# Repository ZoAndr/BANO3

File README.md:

# BANO3
Board Aviation Anticollision Navigation Lights Version 3

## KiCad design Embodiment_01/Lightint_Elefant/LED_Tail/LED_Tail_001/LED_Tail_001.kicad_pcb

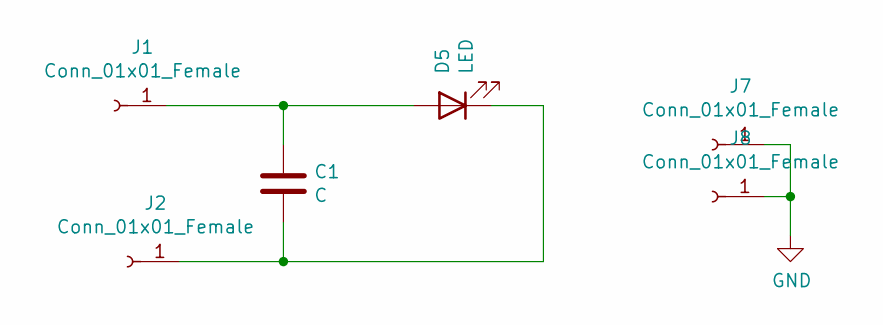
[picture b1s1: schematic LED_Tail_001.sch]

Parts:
C1: C; C_0805_2012Metric_Pad1.18x1.45mm_HandSolder
D5: LED; LED_Cree-XHP35
J1, J2: Conn_01x01_Female; pin_0.8
J7, J8: Conn_01x01_Female; pin_1.5

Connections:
GND: J7.1, J8.1
unnamed: C1.1, D5.2 (A), J1.1
unnamed: C1.2, D5.1 (K), J2.1

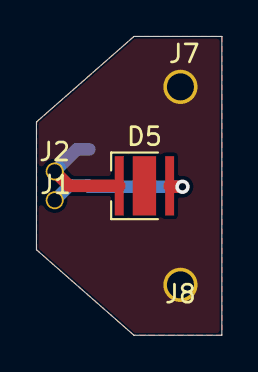
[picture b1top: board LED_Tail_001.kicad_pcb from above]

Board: 2 copper layers, 10.3 x 16.6 mm, 6 parts (1 on the bottom side), 3 nets.

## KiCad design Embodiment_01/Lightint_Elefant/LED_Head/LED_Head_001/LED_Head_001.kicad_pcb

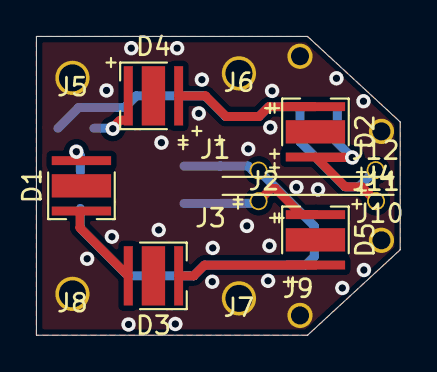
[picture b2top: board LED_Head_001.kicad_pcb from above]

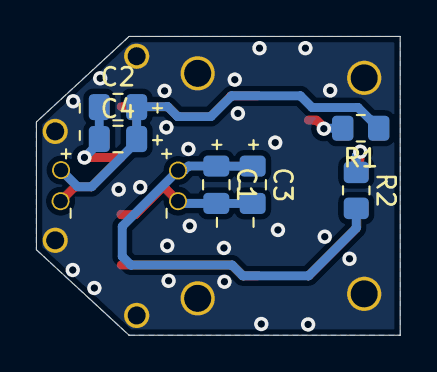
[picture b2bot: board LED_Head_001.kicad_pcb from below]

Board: 2 copper layers, 20.2 x 16.6 mm, 23 parts (6 on the bottom side), 10 nets.

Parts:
C1, C2, C3, C4: C; C_0805_2012Metric_Pad1.18x1.45mm_HandSolder
D1, D2, D3, D4, D5: LED; LED_Cree-XHP35
J1, J2, J11, J12: Conn_01x01_Female; pin_0.8
J3, J4, J9, J10: Conn_01x01_Female; pin_1.0
J5, J6, J7, J8: Conn_01x01_Female; pin_1.5
R1, R2: R; R_0805_2012Metric_Pad1.20x1.40mm_HandSolder

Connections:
GND: J3.1, J4.1, J5.1, J6.1, J7.1, J8.1, J9.1, J10.1
unnamed: C1.1, C3.1, J1.1, R2.2
unnamed: C1.2, C3.2, D5.1, J2.1
unnamed: C2.1, C4.1, D2.2, J11.1
unnamed: C2.2, C4.2, J12.1, R1.1
unnamed: D1.1, D3.2
unnamed: D1.2, R2.1
unnamed: D2.1, D4.2
unnamed: D3.1, D5.2
unnamed: D4.1, R1.2

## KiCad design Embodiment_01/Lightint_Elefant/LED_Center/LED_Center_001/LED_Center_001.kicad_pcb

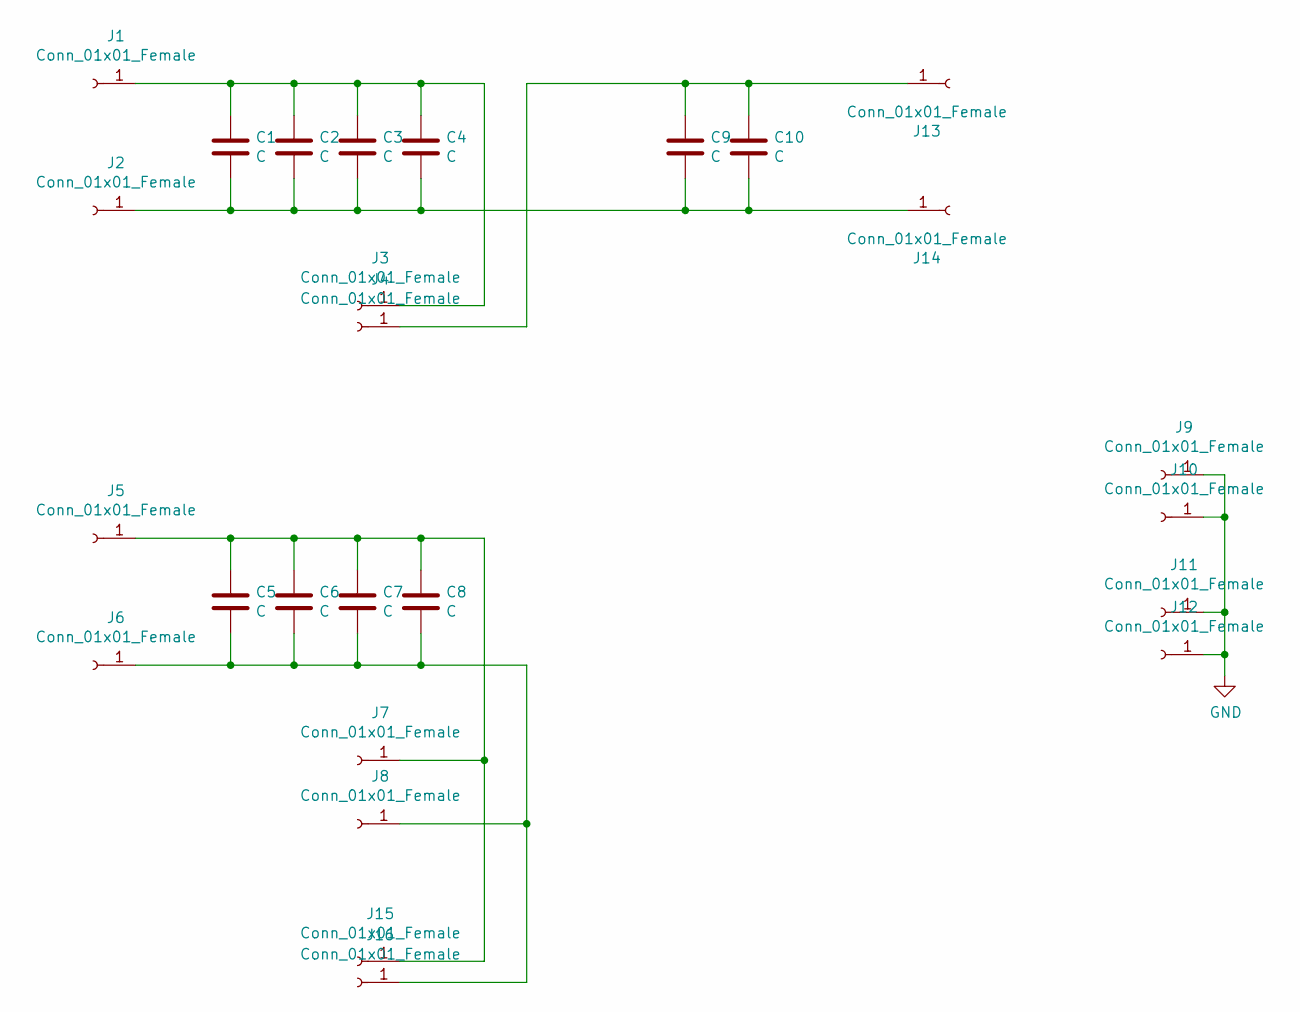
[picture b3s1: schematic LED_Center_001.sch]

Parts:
C1, C2, C3, C4, C5, C6, C7, C8, C9, C10: C; C_0805_2012Metric_Pad1.18x1.45mm_HandSolder
J1, J2, J5, J6, J13, J14: Conn_01x01_Female; WireSidePlate_001
J3, J4, J7, J8, J15, J16: Conn_01x01_Female; pin_0.8
J9, J10, J11, J12: Conn_01x01_Female; pin_1.0

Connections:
GND: J9.1, J10.1, J11.1, J12.1
unnamed: C1.1, C2.1, C3.1, C4.1, J1.1, J3.1
unnamed: C1.2, C2.2, C3.2, C4.2, C9.2, C10.2, J2.1, J14.1
unnamed: C5.1, C6.1, C7.1, C8.1, J5.1, J7.1, J15.1
unnamed: C5.2, C6.2, C7.2, C8.2, J6.1, J8.1, J16.1
unnamed: C9.1, C10.1, J4.1, J13.1

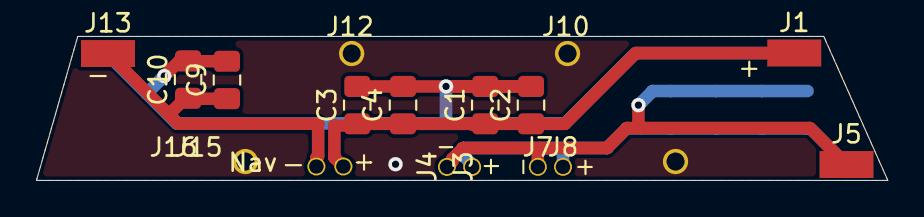
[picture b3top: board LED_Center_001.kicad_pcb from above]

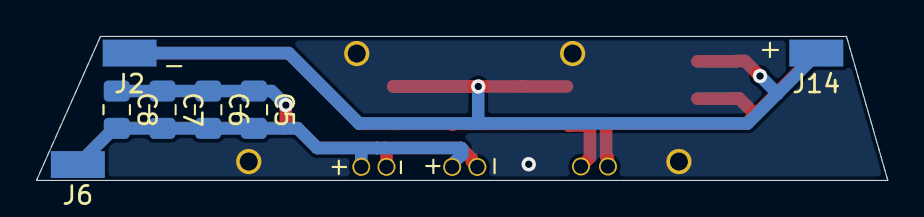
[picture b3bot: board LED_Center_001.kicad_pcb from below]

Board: 2 copper layers, 47.3 x 8.0 mm, 26 parts (7 on the bottom side), 6 nets.

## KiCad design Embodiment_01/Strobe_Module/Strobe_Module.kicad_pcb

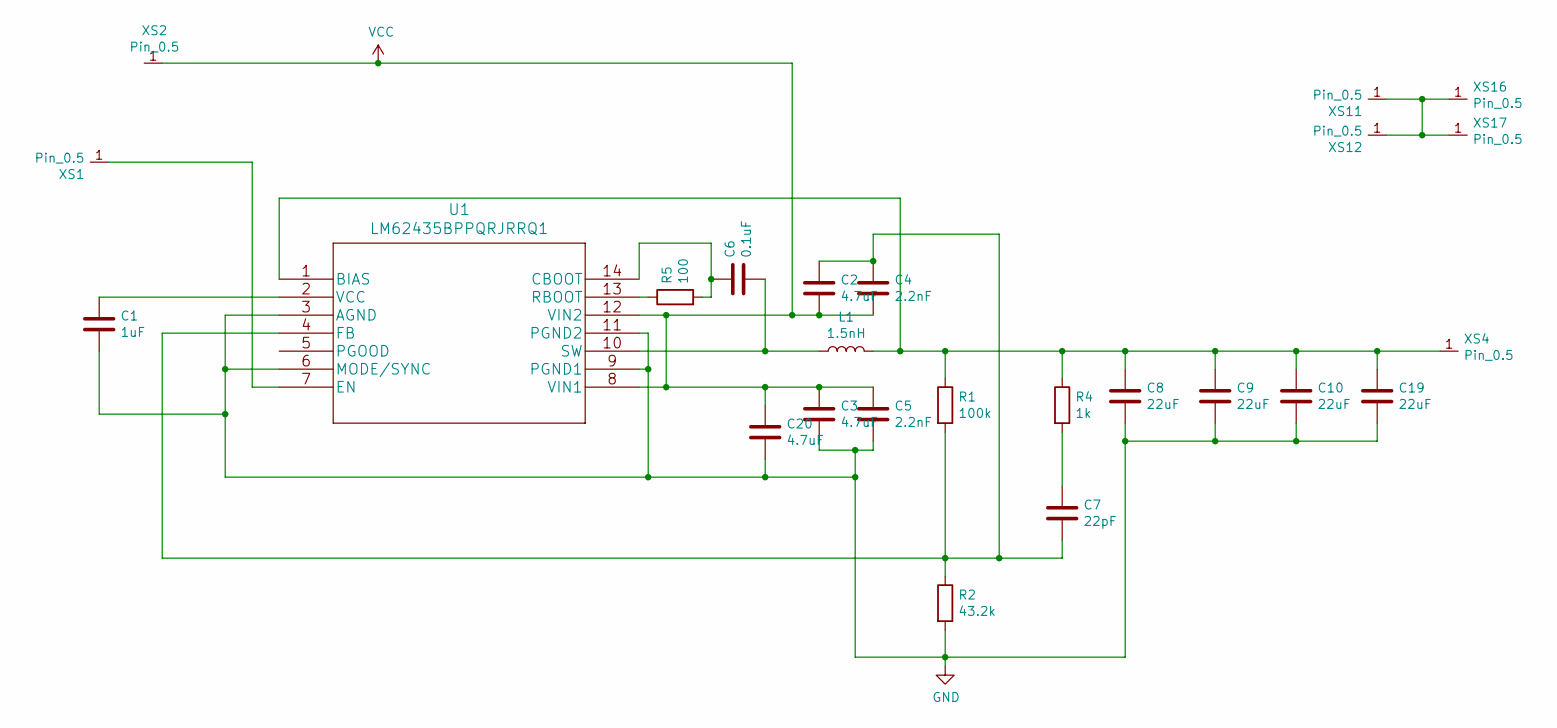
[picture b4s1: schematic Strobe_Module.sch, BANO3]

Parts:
C1: 1uF; C_0603_1608Metric
C2, C3, C20: 4.7uF; C_0805_2012Metric
C4, C5: 2.2nF; C_0603_1608Metric
C6: 0.1uF; C_0603_1608Metric
C7: 22pF; C_0603_1608Metric
C8, C9, C10, C19: 22uF; C_0805_2012Metric
L1: 1.5nH; L_Bourns-SRN6028
R1: 100k; R_0603_1608Metric
R2: 43.2k; R_0603_1608Metric
R4: 1k; R_0603_1608Metric
R5: 100; R_0603_1608Metric
U1: LM62435BPPQRJRRQ1
XS1, XS2, XS4, XS11, XS12, XS16, XS17: Pin_0.5; pin_0.8

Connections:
GND: C1.2, C3.2, C5.2, C8.2, C9.2, C10.2, C19.2, C20.2, R2.2, U1.3 (AGND), U1.6 (MODE/SYNC), U1.9 (PGND1), U1.11 (PGND2)
unnamed: C1.1, U1.2 (VCC)
unnamed: C2.1, C4.1, C7.2, R1.2, R2.1, U1.4 (FB)
unnamed: C6.1, R5.2, U1.14 (CBOOT)
unnamed: C6.2, L1.1, U1.10 (SW)
unnamed: C7.1, R4.2
unnamed: C8.1, C9.1, C10.1, C19.1, L1.2, R1.1, R4.1, U1.1 (BIAS), XS4.1
unnamed: R5.1, U1.13 (RBOOT)
unnamed: U1.7 (EN), XS1.1
unnamed: XS11.1, XS12.1, XS16.1, XS17.1
VCC: C2.2, C3.1, C4.2, C5.1, C20.1, U1.8 (VIN1), U1.12 (VIN2), XS2.1

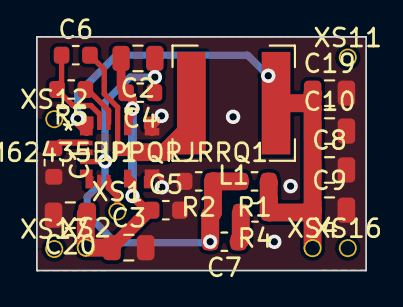
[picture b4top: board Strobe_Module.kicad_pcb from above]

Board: 2 copper layers, 18.3 x 13.0 mm, 25 parts (0 on the bottom side), 11 nets.

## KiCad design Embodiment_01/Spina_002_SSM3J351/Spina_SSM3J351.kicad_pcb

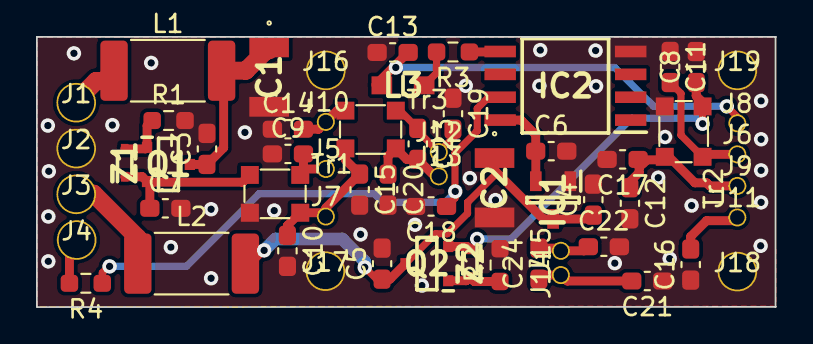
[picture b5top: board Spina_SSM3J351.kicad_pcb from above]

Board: 2 copper layers, 41.0 x 15.0 mm, 59 parts (0 on the bottom side), 25 nets.

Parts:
C1, C2: C; C3225_Commercial
C3, C4, C5, C6, C7, C8, C9, C10, C11, C12, C13, C14, C15, C16, C17, C18, C19, C20, C21, C22, C23, C24: C; C_0603_1608Metric_Pad1.08x0.95mm_HandSolder
IC1: ZXTR2105FQ-7; SOT96P240X110-3N
IC2: ATTINY25-20SH; SOIC127P798X216-8N
J1, J2, J3, J4, J16, J17, J18, J19: Conn_01x01; pin_2.0
J5, J6, J7, J8, J9, J10, J11, J12, J13, J14, J15: Conn_01x01; pin_0.8
L1, L2: SNR6045K-1R0N; L_2512_6332Metric_Pad1.52x3.35mm_HandSolder
L3: L; LQM21DN220N00L
Q1, Q2: SSM3J351R,LF; SOTFL95P240X88-3N
R1, R2, R3, R4: R; R_0603_1608Metric_Pad0.98x0.95mm_HandSolder
Tr1, Tr2, Tr3: CMF3225
Z1, Z2: BZT52C12TQ-7-F; SODFL1608X65N

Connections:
GND: C1.2, C2.2, C3.2, C4.2, C5.2, C6.2, C7.2, C8.2, C9.1, C10.2, C11.1, C12.2, C13.1, C14.1, C15.2, C16.1, C17.2, C18.2, C19.1, C20.2, C21.1, C22.2, IC1.1, IC2.4, J2.1, J16.1, J17.1, J18.1, J19.1, R1.2, R2.2, Tr1.2, Tr2.2
GND1: C12.1, C17.1, J9.1, Tr2.4
GND2: C22.1, C24.2, J15.1
GND3: C10.1, C15.1, J7.1, Tr1.4, Tr3.2
GNDA: C20.1, C23.2, J13.1, Tr3.4
unnamed: C1.1, C3.1, L1.2, Q1.3
unnamed: C2.1, C4.1, C5.1, IC1.3, L2.2, Q2.3
unnamed: C6.1, IC1.2, IC2.8
unnamed: C7.1, Q1.2, Tr1.1, Z1.1
unnamed: C8.1, Q2.2, Tr2.1, Z2.1
unnamed: C9.2, J5.1, Tr1.3
unnamed: C11.2, J6.1, Tr2.3
unnamed: C13.2, J8.1, L3.2
unnamed: C14.2, J10.1, Tr3.1
unnamed: C16.2, J11.1
unnamed: C18.1, IC2.7, R4.1
unnamed: C19.2, C23.1, J12.1, Tr3.3
unnamed: C21.2, C24.1, J14.1
unnamed: IC2.5, R3.1
unnamed: J1.1, L1.1
unnamed: J3.1, L2.1
unnamed: J4.1, R4.2
unnamed: L3.1, R3.2
unnamed: Q1.1, R1.1, Z1.2
unnamed: Q2.1, R2.1, Z2.2

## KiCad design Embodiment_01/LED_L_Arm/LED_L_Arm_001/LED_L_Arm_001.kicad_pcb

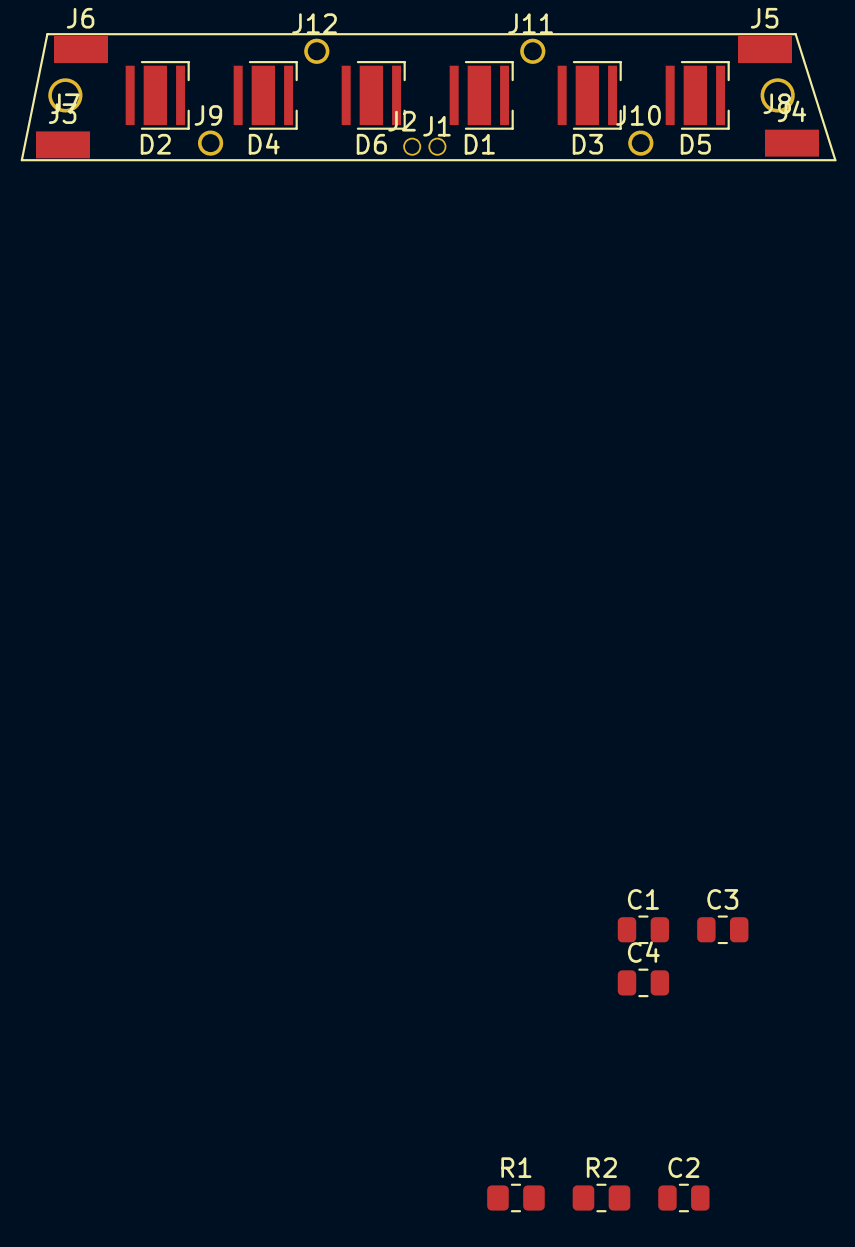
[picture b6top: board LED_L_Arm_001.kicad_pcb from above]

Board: 2 copper layers, 24 parts (0 on the bottom side), 9 nets, no tracks yet.

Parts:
C1, C2, C3, C4: C; R_0805_2012Metric
D1, D2, D3, D4, D5, D6: LED; LED_Cree-XHP35
J1, J2: Conn_01x01_Female; pin_0.8
J3, J4, J5, J6: Conn_01x01_Female; WireSidePlate_001
J7, J8: Conn_01x01_Female; pin_1.5
J9, J10, J11, J12: Conn_01x01_Female; pin_1.0
R1, R2: R; R_0805_2012Metric_Pad1.20x1.40mm_HandSolder

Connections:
GND: J3.1, J4.1, J5.1, J6.1, J7.1, J8.1, J9.1, J10.1, J11.1, J12.1
unnamed: C1.1, C2.1, C3.1, C4.1, D1.2, D2.2, J1.1
unnamed: C1.2, C2.2, C3.2, C4.2, J2.1, R1.1, R2.1
unnamed: D1.1, D3.2
unnamed: D2.1, D4.2
unnamed: D3.1, D5.2
unnamed: D4.1, D6.2
unnamed: D5.1, R1.2
unnamed: D6.1, R2.2

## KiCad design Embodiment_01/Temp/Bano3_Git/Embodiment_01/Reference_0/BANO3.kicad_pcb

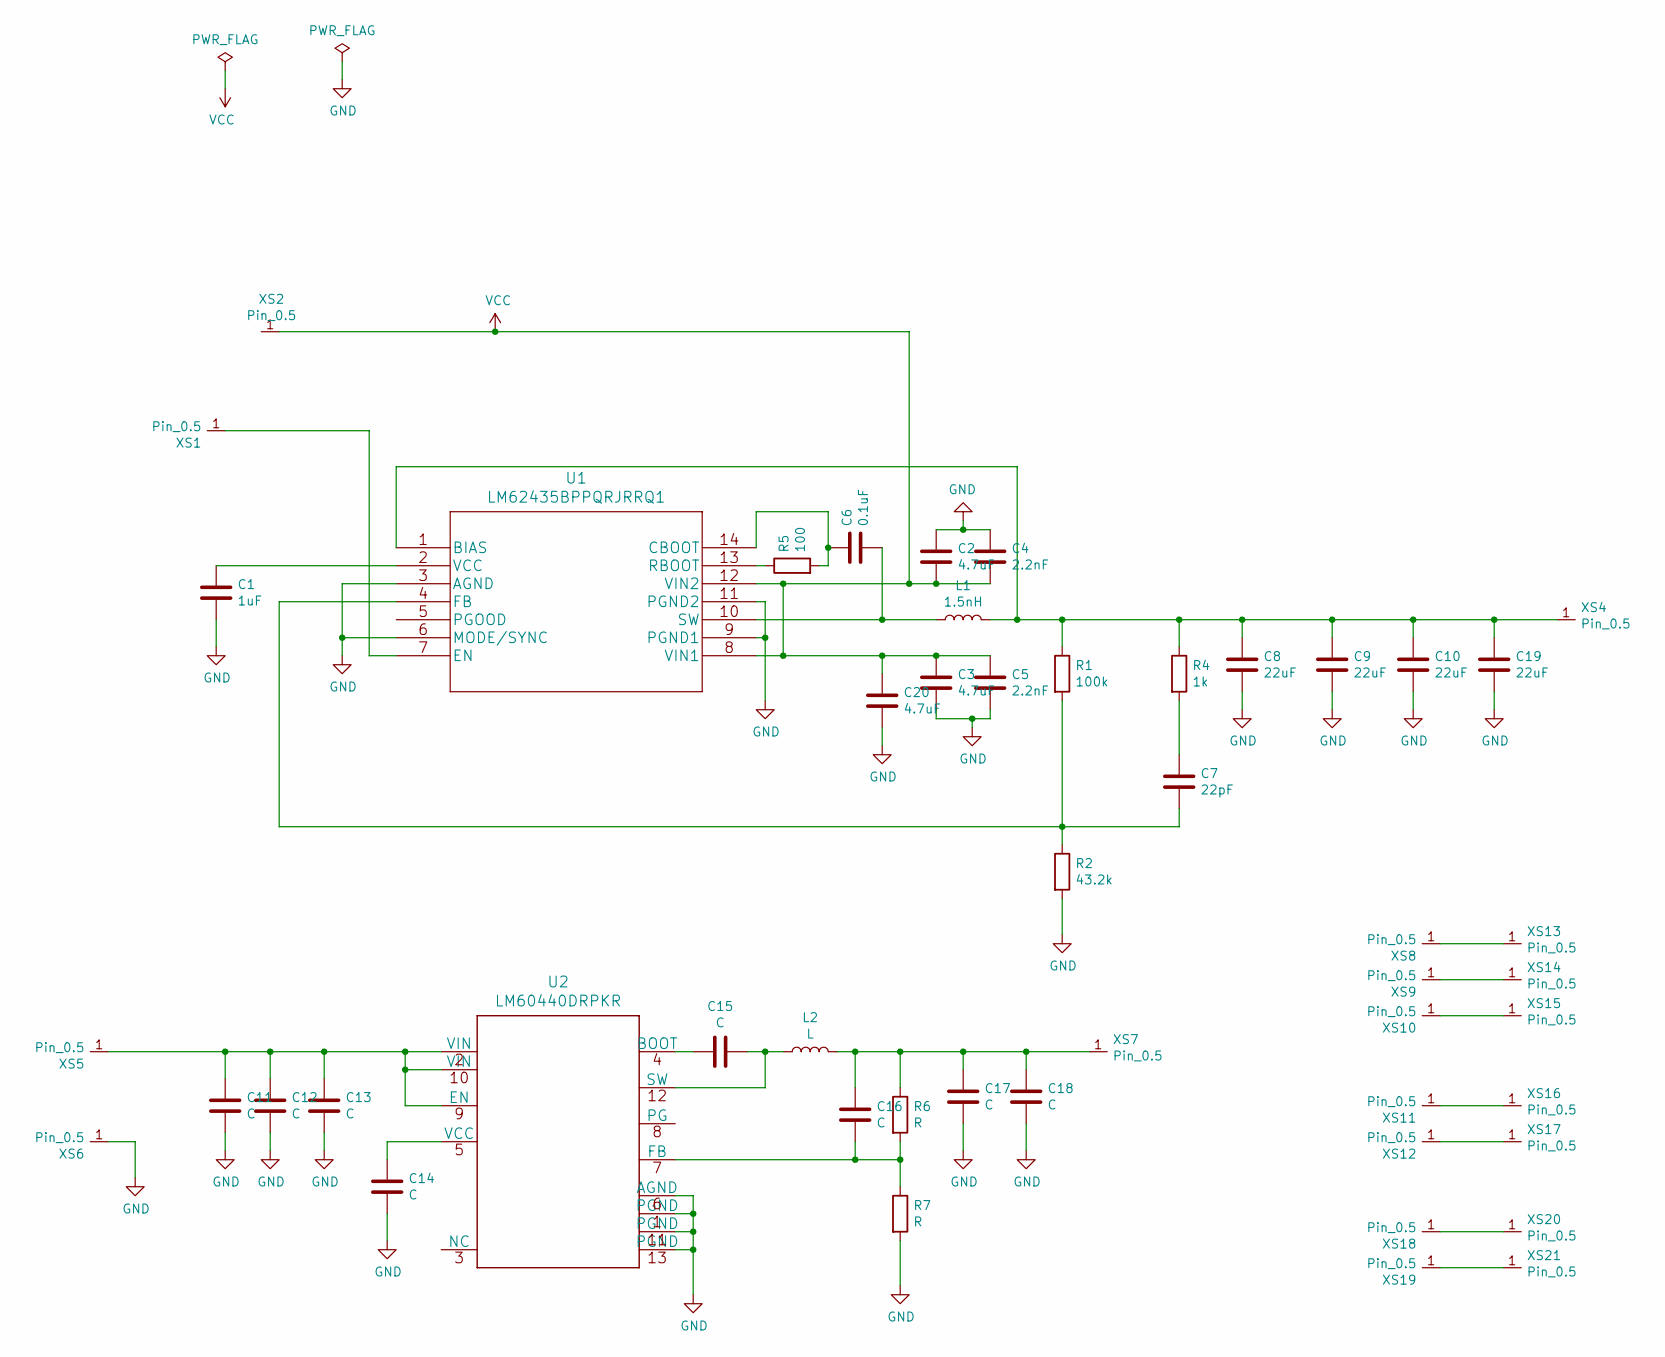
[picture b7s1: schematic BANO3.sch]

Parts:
C1: 1uF; C_0603_1608Metric
C2, C3, C20: 4.7uF; C_0805_2012Metric
C4, C5: 2.2nF; C_0603_1608Metric
C6: 0.1uF; C_0603_1608Metric
C7: 22pF; C_0603_1608Metric
C8, C9, C10, C19: 22uF; C_0805_2012Metric
C11, C17, C18: C; C_0805_2012Metric_Pad1.15x1.40mm_HandSolder
C12, C13, C14, C15, C16: C; C_0603_1608Metric_Pad1.05x0.95mm_HandSolder
L1: 1.5nH; L_Bourns-SRN6028
L2: L; L_1210_3225Metric_Pad1.42x2.65mm_HandSolder
R1: 100k; R_0603_1608Metric
R2: 43.2k; R_0603_1608Metric
R4: 1k; R_0603_1608Metric
R5: 100; R_0603_1608Metric
R6, R7: R; L_0603_1608Metric_Pad1.05x0.95mm_HandSolder
U1: LM62435BPPQRJRRQ1
U2: LM60440DRPKR
XS1, XS2, XS4, XS5, XS6, XS7, XS11, XS12, XS13, XS14, XS15, XS16, XS17: Pin_0.5; pin_0.8
XS8, XS9, XS10: Pin_0.5; Plate_1
XS18, XS19, XS20, XS21: Pin_0.5; pin_2.2

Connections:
GND: C1.2, C2.1, C3.2, C4.1, C5.2, C8.2, C9.2, C10.2, C11.2, C12.2, C13.2, C14.2, C17.2, C18.2, C19.2, C20.2, R2.2, R7.2, U1.3 (AGND), U1.6 (MODE/SYNC), U1.9 (PGND1), U1.11 (PGND2), U2.1 (PGND), U2.6 (AGND), U2.11 (PGND), U2.13 (PGND), XS6.1
unnamed: C1.1, U1.2 (VCC)
unnamed: C6.1, R5.2, U1.14 (CBOOT)
unnamed: C6.2, L1.1, U1.10 (SW)
unnamed: C7.1, R4.2
unnamed: C7.2, R1.2, R2.1, U1.4 (FB)
unnamed: C8.1, C9.1, C10.1, C19.1, L1.2, R1.1, R4.1, U1.1 (BIAS), XS4.1
unnamed: C11.1, C12.1, C13.1, U2.2 (VIN), U2.9 (EN), U2.10 (VIN), XS5.1
unnamed: C14.1, U2.5 (VCC)
unnamed: C15.1, L2.1, U2.12 (SW)
unnamed: C15.2, U2.4 (BOOT)
unnamed: C16.1, C17.1, C18.1, L2.2, R6.1, XS7.1
unnamed: C16.2, R6.2, R7.1, U2.7 (FB)
unnamed: R5.1, U1.13 (RBOOT)
unnamed: U1.7 (EN), XS1.1
unnamed: XS10.1, XS15.1
unnamed: XS11.1, XS16.1
unnamed: XS12.1, XS17.1
unnamed: XS8.1, XS13.1
unnamed: XS9.1, XS14.1
unnamed: XS18.1, XS20.1
unnamed: XS19.1, XS21.1
VCC: C2.2, C3.1, C4.2, C5.1, C20.1, U1.8 (VIN1), U1.12 (VIN2), XS2.1

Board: 2 copper layers, 50 parts (0 on the bottom side), 23 nets, no tracks yet.

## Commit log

2021-07-10 Init
2021-08-17 Reinit
2021-08-20 LED and fixing holes added
2021-08-22 Calculation of shape, PCB
2021-08-25 elefant wings added
2021-08-27 Lighting eq assembled
2021-08-28 Gerbers ready

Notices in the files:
parts and their libraries:
Copyright 2021 Accelerated Designs. All rights reserved.
